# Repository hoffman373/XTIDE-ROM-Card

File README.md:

# XTIDE-ROM-Card

An 8-bit ISA card that holds a 27C256 EPROM as an option ROM in the upper memory area of a PC/XT-class machine, typically to load the [XTIDE Universal BIOS](https://www.xtideuniversalbios.org/).

The schematic is a redraw of Dan Hoover's "The $4 XTIDE" concept.

## Overview

- **ROM:** 27C256 (32 KB) EPROM in a 28-pin DIP socket
- **Address decode:** 74LS688 8-bit comparator in a 20-pin DIP socket
- **Address select:** 2x4 pin header (J1) with a SIP-5 pull-up resistor network (RN1)
- **Bus connector:** 8-bit ISA edge connector (`Bus_ISA_8bit`)
- **Decoupling:** 100 nF disc capacitors on each IC

### How it works

The 74LS688 compares A19-A15 against the levels set on J1. It also requires AEN low (no DMA cycle) and /MEMR low (memory read). When everything matches, it pulls `ROM_SEL` low and the EPROM drives D0-D7 for the read.

A19 is tied to match 1, so the 32 KB window always falls between 80000h and FFFFFh. RN1 pulls `SEL_A15` to `SEL_A18` high. Installing a jumper pulls that bit low.

### Address selection

| J1 pins | Address bit |
|---|---|
| 1-2 | A15 |
| 3-4 | A16 |
| 5-6 | A17 |
| 7-8 | A18 |

Jumper **in** = 0, jumper **out** = 1.

| ROM base | A18 | A17 | A16 | A15 | Jumpers installed |
|---|---|---|---|---|---|
| C8000h | 1 | 0 | 0 | 1 | 3-4, 5-6 |
| D0000h | 1 | 0 | 1 | 0 | 1-2, 5-6 |
| D8000h | 1 | 0 | 1 | 1 | 5-6 |
| E0000h | 1 | 1 | 0 | 0 | 1-2, 3-4 |
| E8000h | 1 | 1 | 0 | 1 | 3-4 |

- Keep the jumper off 7-8. A18 = 0 maps the ROM into A0000h-BFFFFh, which is video memory.
- C0000h is normally taken by the video BIOS.
- Pick a window that doesn't overlap video memory, a hard disk controller BIOS, or any other option ROM in the machine.

## Opening the project

1. Install [KiCad](https://www.kicad.org/) 10 or newer. The files use the KiCad 10 format and will not open in older versions.
2. Clone the repository:
   ```
   git clone https://github.com/hoffman373/XTIDE-ROM-Card.git
   ```
3. Open `xtide_rom_card.kicad_pro`.

Custom footprints live in `lib/footprints/` and are registered through the project's `fp-lib-table` using `${KIPRJMOD}`, so no library setup is needed. Everything else uses stock KiCad symbols and footprints.

## Programming the ROM

Burn the ROM image (for example, an XTIDE Universal BIOS build configured for your controller) to a 27C256 with any EPROM programmer. If the image is smaller than 32 KB, pad it to 32 KB with `FFh`. The BIOS checksum must be valid or the system BIOS will skip the ROM during its option ROM scan.

## License

CC BY-SA 4.0, share-alike with the original $4 XTIDE design.

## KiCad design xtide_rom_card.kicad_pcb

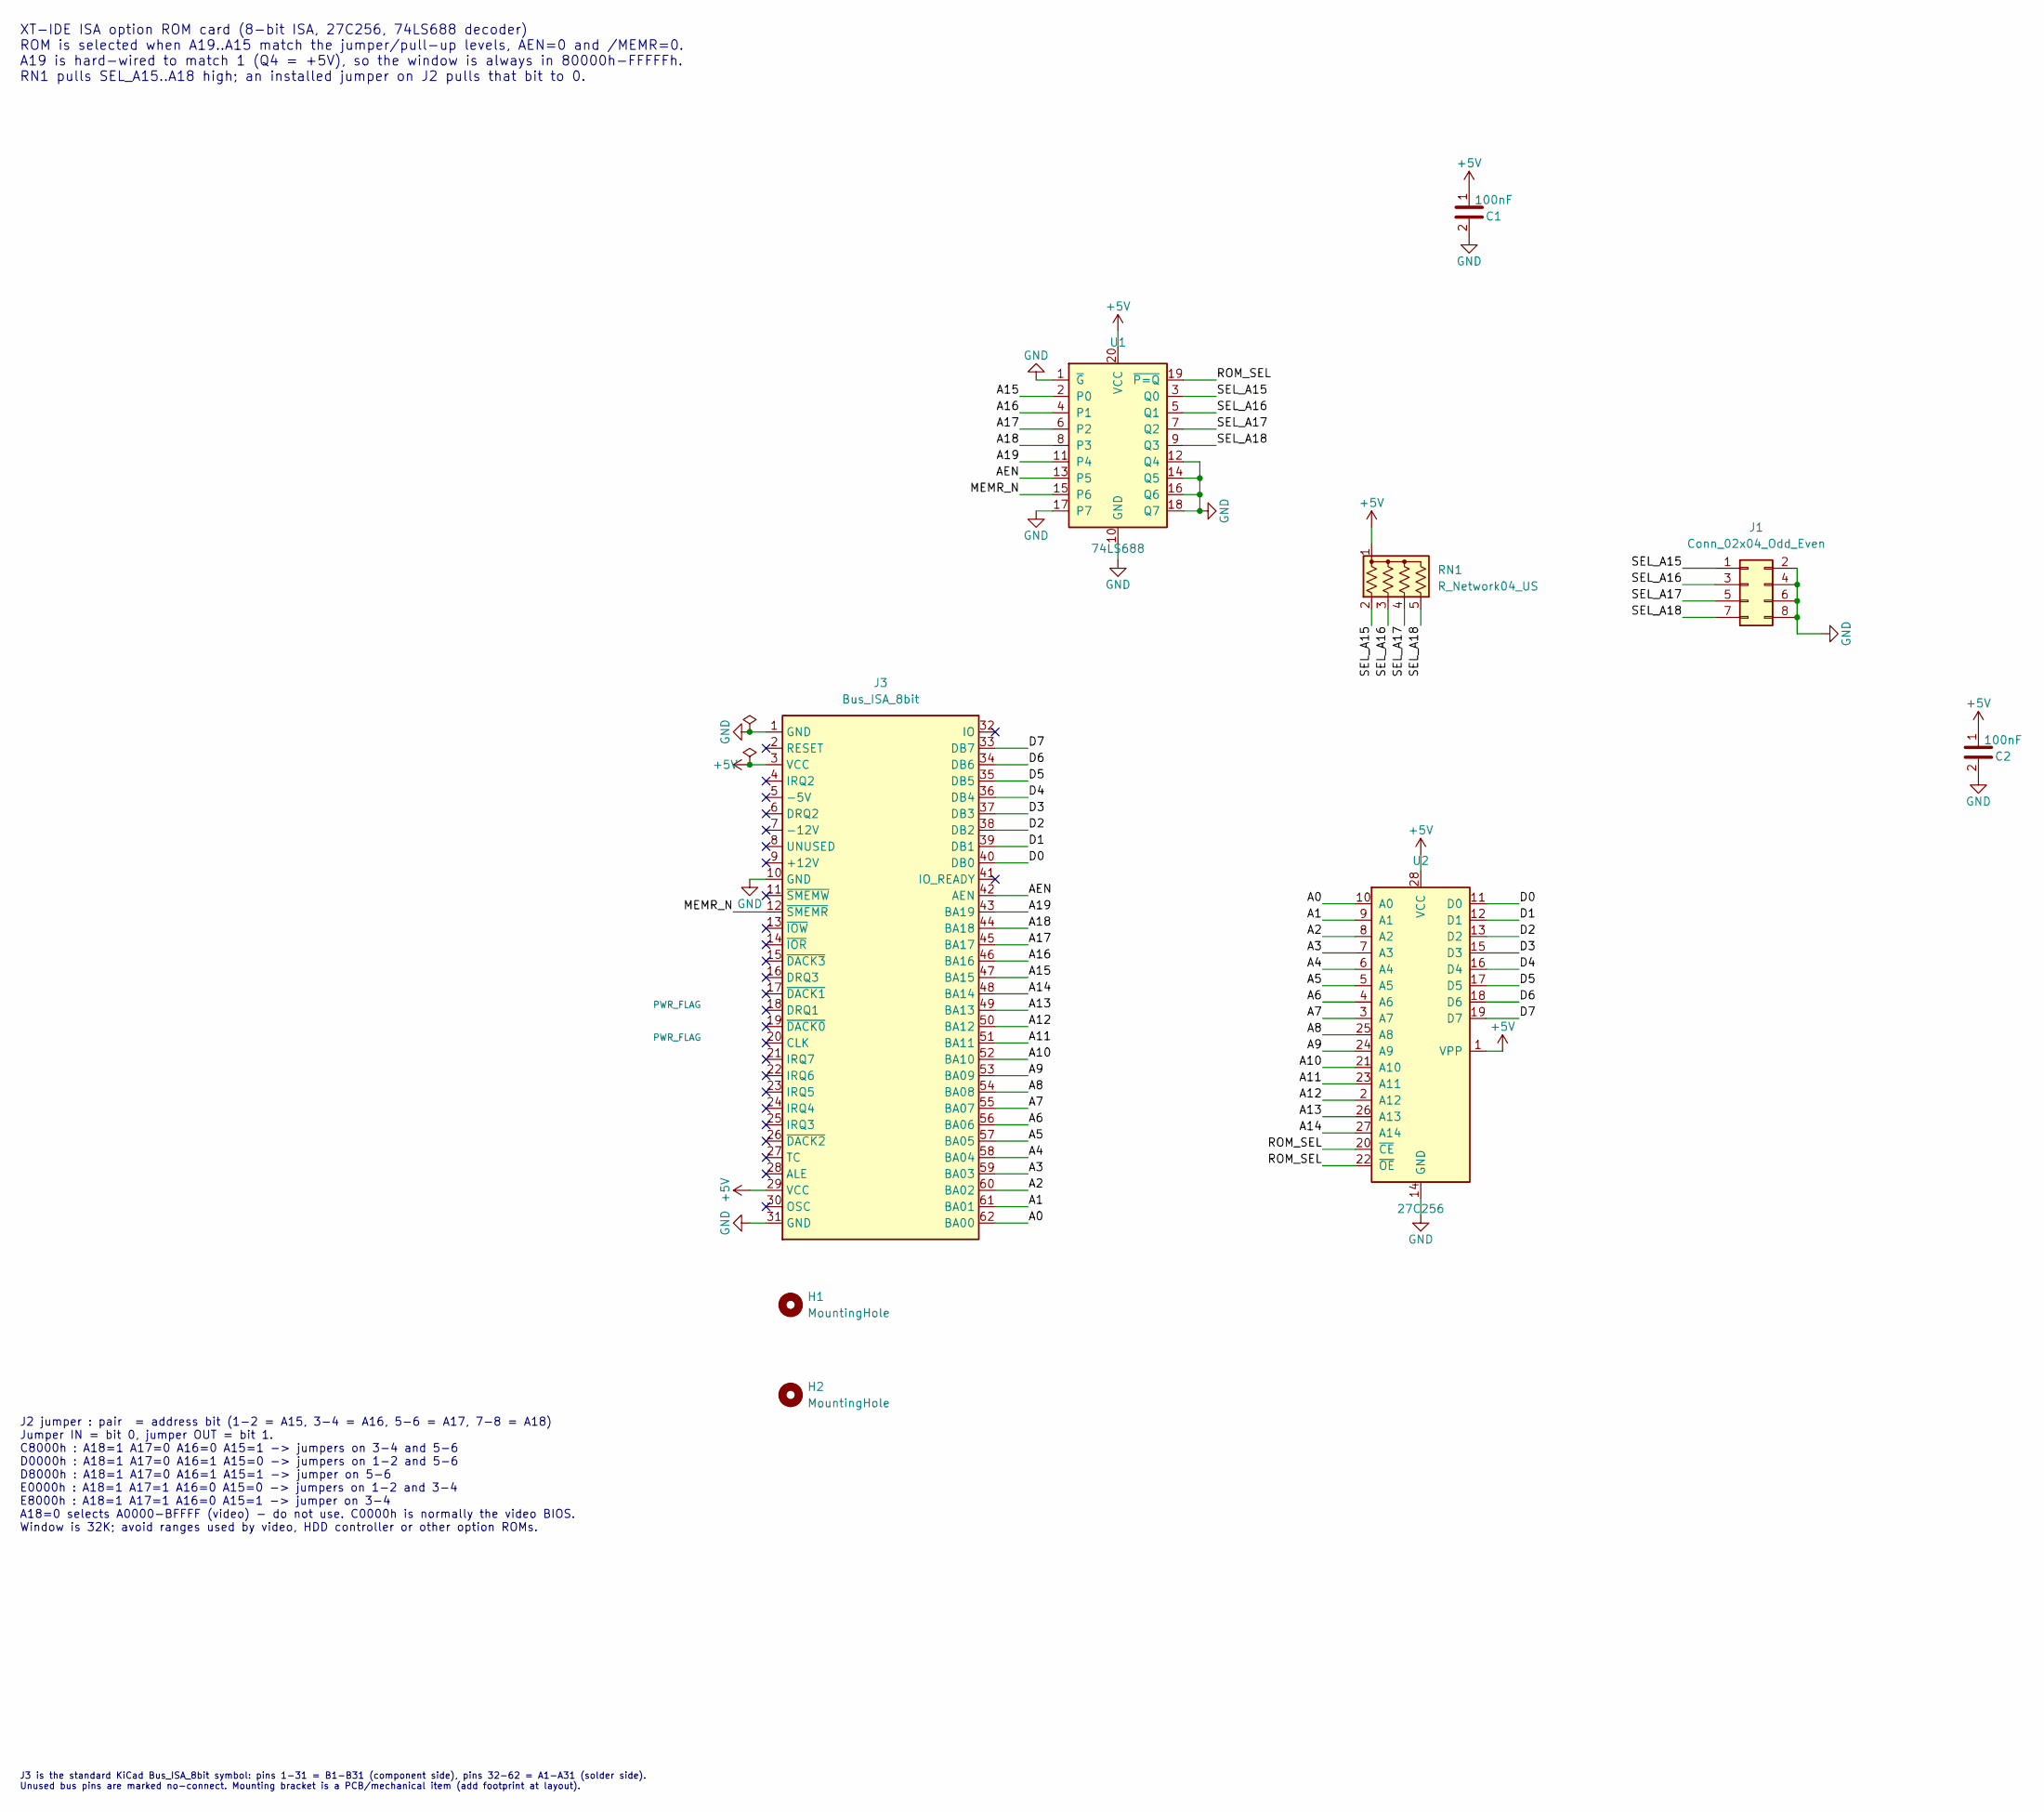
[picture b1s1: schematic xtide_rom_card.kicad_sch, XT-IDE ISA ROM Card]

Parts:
C1, C2: 100nF; C_Disc_D5.0mm_W2.5mm_P5.00mm
H1, H2: MountingHole; MountingHole_3.2mm_M3
J1: Conn_02x04_Odd_Even; PinHeader_2x04_P2.54mm_Vertical
J3: Bus_ISA_8bit; PC_AT_8BIT
RN1: R_Network04_US; R_Array_SIP5
U1: 74LS688; DIP-20_W7.62mm_Socket
U2: 27C256; DIP-28_W15.24mm_Socket

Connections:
+5V: C1.1, C2.1, J3.3 (VCC), J3.29 (VCC), RN1.1 (common), U1.20 (VCC), U2.1 (VPP), U2.28 (VCC)
/A0: J3.62 (BA00), U2.10 (A0)
/A1: J3.61 (BA01), U2.9 (A1)
/A2: J3.60 (BA02), U2.8 (A2)
/A3: J3.59 (BA03), U2.7 (A3)
/A4: J3.58 (BA04), U2.6 (A4)
/A5: J3.57 (BA05), U2.5 (A5)
/A6: J3.56 (BA06), U2.4 (A6)
/A7: J3.55 (BA07), U2.3 (A7)
/A8: J3.54 (BA08), U2.25 (A8)
/A9: J3.53 (BA09), U2.24 (A9)
/A10: J3.52 (BA10), U2.21 (A10)
/A11: J3.51 (BA11), U2.23 (A11)
/A12: J3.50 (BA12), U2.2 (A12)
/A13: J3.49 (BA13), U2.26 (A13)
/A14: J3.48 (BA14), U2.27 (A14)
/A15: J3.47 (BA15), U1.2 (P0)
/A16: J3.46 (BA16), U1.4 (P1)
/A17: J3.45 (BA17), U1.6 (P2)
/A18: J3.44 (BA18), U1.8 (P3)
/A19: J3.43 (BA19), U1.11 (P4)
/AEN: J3.42 (AEN), U1.13 (P5)
/D0: J3.40 (DB0), U2.11 (D0)
/D1: J3.39 (DB1), U2.12 (D1)
/D2: J3.38 (DB2), U2.13 (D2)
/D3: J3.37 (DB3), U2.15 (D3)
/D4: J3.36 (DB4), U2.16 (D4)
/D5: J3.35 (DB5), U2.17 (D5)
/D6: J3.34 (DB6), U2.18 (D6)
/D7: J3.33 (DB7), U2.19 (D7)
/MEMR_N: J3.12 (~SMEMR), U1.15 (P6)
/ROM_SEL: U1.19 (~P=Q), U2.20 (~CE), U2.22 (~OE)
/SEL_A15: J1.1, RN1.2 (R1), U1.3 (Q0)
/SEL_A16: J1.3, RN1.3 (R2), U1.5 (Q1)
/SEL_A17: J1.5, RN1.4 (R3), U1.7 (Q2)
/SEL_A18: J1.7, RN1.5 (R4), U1.9 (Q3)
GND: C1.2, C2.2, J1.2, J1.4, J1.6, J1.8, J3.1 (GND), J3.10 (GND), J3.31 (GND), U1.1 (~G), U1.10 (GND), U1.12 (Q4), U1.14 (Q5), U1.16 (Q6), U1.17 (P7), U1.18 (Q7), U2.14 (GND)

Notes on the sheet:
J3 is the standard KiCad Bus_ISA_8bit symbol: pins 1-31 = B1-B31 (component side), pins 32-62 = A1-A31 (solder side). Unused bus pins are marked no-connect. Mounting bracket is a PCB/mechanical item (add footprint at layout).
J2 jumper : pair = address bit (1-2 = A15, 3-4 = A16, 5-6 = A17, 7-8 = A18) Jumper IN = bit 0, jumper OUT = bit 1. C8000h : A18=1 A17=0 A16=0 A15=1 -> jumpers on 3-4 and 5-6 D0000h : A18=1 A17=0 A16=1 A15=0 -> jumpers on 1-2 and 5-6 D8000h : A18=1 A17=0 A16=1 A15=1 -> jumper on 5-6 E0000h : A18=1 A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
XT-IDE ISA option ROM card (8-bit ISA, 27C256, 74LS688 decoder) ROM is selected when A19..A15 match the jumper/pull-up levels, AEN=0 and /MEMR=0. A19 is hard-wired to match 1 (Q4 = +5V), so the window is always in 80000h-FFFFFh. RN1 pulls SEL_A15..A18 high; an installed jumper on J2 pulls that bit 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

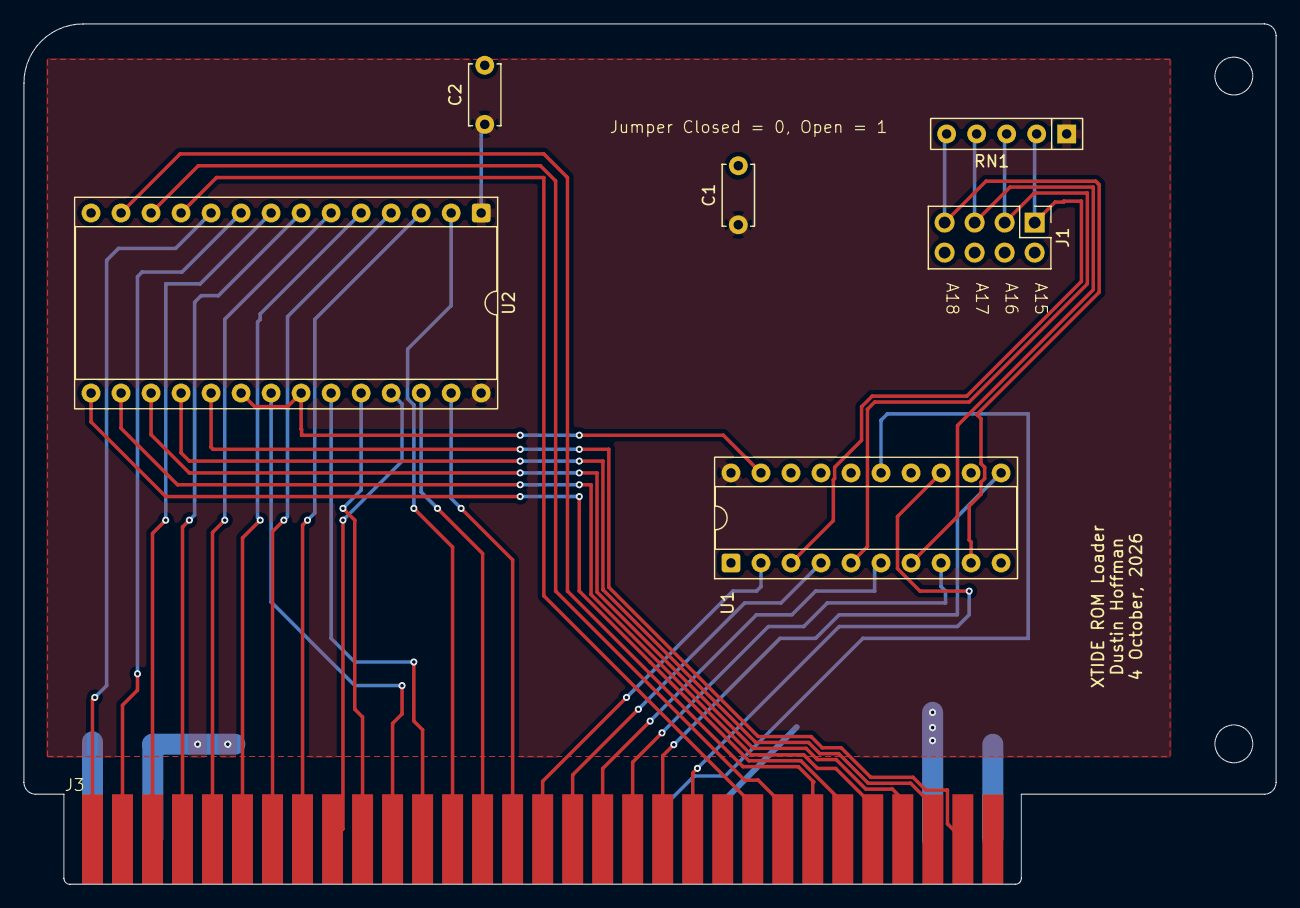
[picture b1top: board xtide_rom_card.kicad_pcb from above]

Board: 2 copper layers, 106.0 x 72.8 mm, 9 parts (0 on the bottom side), 37 nets.

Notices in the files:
xtide_rom_card.kicad_sch:
Concept: Dan Hoover The $4 XTIDE (CC BY-SA) - re-drawn schematic
License: CC BY-SA 4.0 (share-alike with original)
